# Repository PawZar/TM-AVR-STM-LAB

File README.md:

# Projekt centrali alarmowej
## TM-AVR-STM-LAB

Centrala alarmowa z hasłem , 6-wejść typu NC oraz wyjściem przekaźnika naruszenia typu NO.

## Cechy projektu:
* MCU: AtMega32A w obudowie TQFP44
* Wyświetlacz 2x16 ze sterownikiem HD44780
* Zasilanie 12V DC-IN Max:1,2A
* Zasilacznie czujek 12V DC ~1A obc.
* Wyjście naruszenia typu NO ~1A obciążenie styków
* Wejścia czujek NC wyzwalane stanem niskim
* Pamięć naruszeń
* Kontrola kontrastu wyświetlacza
* Diody LED statusu centrali (alarm,uzbrojenie,stan spoczynku,odliczanie)
* 6 przycisków w roli klawiatury (ESC,1-4,ENTER)
* Dioda LED zasilania

## Działanie centrali:

Centrala posiada 2 tryby, uzbrojony oraz nieuzbrojony. Po wciśnięciu przycisku ENTER następuje przejście do funkcji wpisywania hasła.
Do wpisywania hasła dostępne mamy przyciski 1-4, ENTER oraz ESC który kasuje błędnie wpisaną liczbę .
Po poprawnym wpisaniu hasła następuje odliczanie 20sekund symulujące czas na wyjście z mieszkania. Po upływie czasu uzbrajania centrali,
wejścia czujek aktywują się. Wejścia ustawione są w tryb NC ze zwarciem do GND, kiedy jedna z czujek przez minimum 1,6sek 
zostanie aktywowana zaczyna się przejście do funkcji wpisywania hasła na które ma się ponowne 20sekund. Po upływie tego czasu,
bądź 3-krotnym złym wpisaniu hasła następuje wyzwolenie alarmu i załączenie wyjścia. Podczas trwanai alarmu można przejść do funkcji 
wpisywania hasła przyciskiem ENTER. Po rozbrojeniu centrali po alarmie zapamiętane zostaje zdarzenie naruszenia systemu, po następnym uzbrojeniu
centrali błąd się kasuje.

## Mikrokontroler Atmega32A:

 * Taktowanie w projekcie: 16MHz zewnętrzne
 * Zasilanie układu: 5V DC
 * Programowanie : złącze ISP
 * 1kB EEPROM
 * 2kB SRAM
 * 32kB flash

## Zdjęcia schematu oraz płytki z programu EAGLE:

## Zdjęcia wykonanego układu:

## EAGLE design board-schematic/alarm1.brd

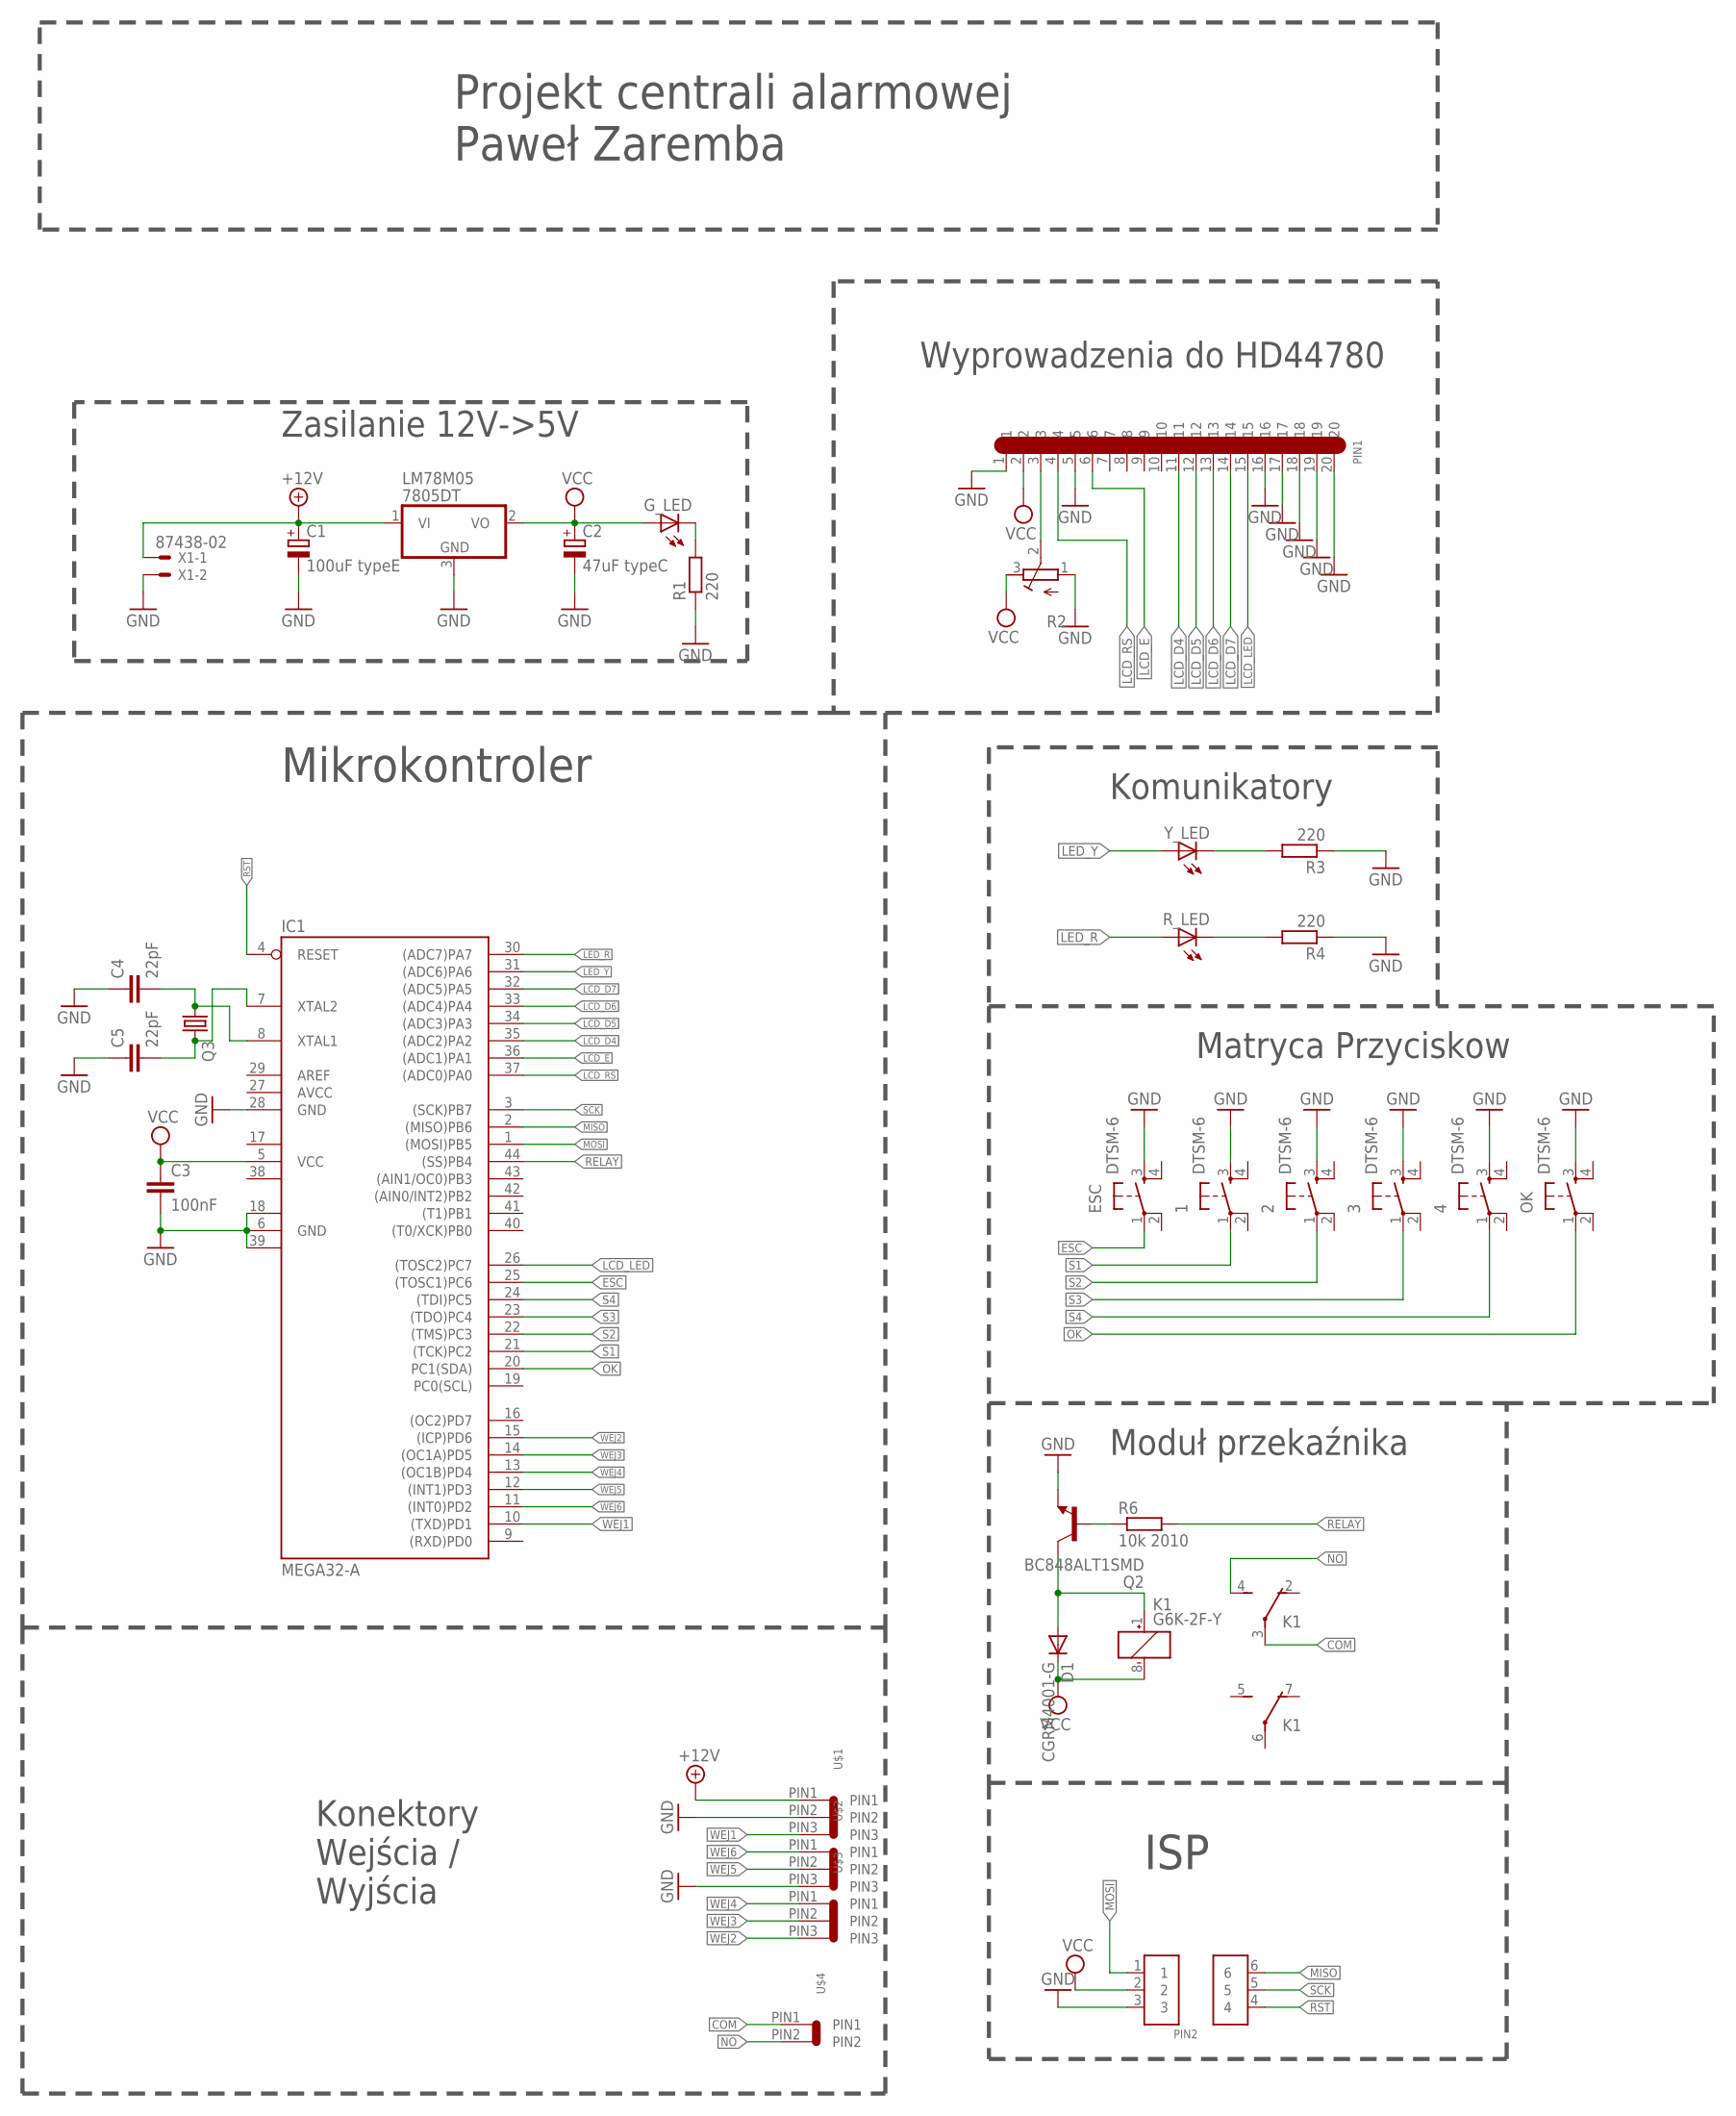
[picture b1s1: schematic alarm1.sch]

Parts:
1, 2, 3, 4: DTSM-6
C1: 100uF typeE; PANASONIC_E
C2: 47uF typeC; PANASONIC_C
C3: 100nF; C1206
C4, C5: 22pF; C1206
D1: CGRM4001-G; SOD-123_MINI-SMA
ESC: DTSM-6
G_LED: LEDCHIPLED_1206; CHIPLED_1206
IC1: MEGA32-A; TQFP44
K1: G6K-2F-Y
LM78M05: 7805DT; TO252
OK: DTSM-6
PIN1: SINGLE1X20
PIN2: 2X3_GOLDPIN; GOLD2X3
Q2: BC848ALT1SMD; SOT23
Q3: CRYSTALHC49UP; HC49UP
R1, R3, R4: 220; R1206
R2: R-TRIMM3314J; RTRIM3314J
R6: 10k 2010; R2010
R_LED: LEDCHIPLED_1206; CHIPLED_1206
U$1, U$2, U$3: GOLDPIN_SMD_1X3; GOLDPINSMD1X3
U$4: GOLDPIN_SMD_1X2; GOLDPINSMD1X2
X1: 87438-02
Y_LED: LEDCHIPLED_1206; CHIPLED_1206

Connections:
+12V: C1.+, LM78M05.1 (VI), U$1.PIN1, X1.1
AVCC: IC1.27 (AVCC)
COM: K1.3, U$4.PIN1
CRYSTAL_L: C5.2, IC1.7 (XTAL2), Q3.2
CRYSTAL_R: C4.2, IC1.8 (XTAL1), Q3.1
ESC: ESC.1, IC1.25 ((TOSC1)PC6)
GND: 1.3, 2.3, 3.3, 4.3, C1.-, C2.-, C3.2, C4.1, C5.1, ESC.3, IC1.6 (GND), IC1.18 (GND1), IC1.28 (GND), IC1.39 (GND2), LM78M05.3 (GND), OK.3, PIN1.1, PIN1.5, PIN1.16, PIN1.17, PIN1.18, PIN1.19, PIN1.20, PIN2.3, Q2.2 (E), R1.1, R2.1 (E), R3.1, R4.1, U$1.PIN2, U$2.PIN3, X1.2
LCD_D4: IC1.35 ((ADC2)PA2), PIN1.11
LCD_D5: IC1.34 ((ADC3)PA3), PIN1.12
LCD_D6: IC1.33 ((ADC4)PA4), PIN1.13
LCD_D7: IC1.32 ((ADC5)PA5), PIN1.14
LCD_E: IC1.36 ((ADC1)PA1), PIN1.6
LCD_LED: IC1.26 ((TOSC2)PC7), PIN1.15
LCD_RS: IC1.37 ((ADC0)PA0), PIN1.4
LED_R: IC1.30 ((ADC7)PA7), R_LED.A
LED_Y: IC1.31 ((ADC6)PA6), Y_LED.A
MISO: IC1.2 ((MISO)PB6), PIN2.6
MOSI: IC1.1 ((MOSI)PB5), PIN2.1
unnamed: D1.A, K1.1 (+), Q2.3 (C)
unnamed: G_LED.C, R1.2
unnamed: PIN1.3, R2.2 (S)
unnamed: R3.2, Y_LED.C
unnamed: R4.2, R_LED.C
unnamed: Q2.1 (B), R6.1
NO: K1.4 (S), U$4.PIN2
OK: IC1.20 (PC1(SDA)), OK.1
RELAY: IC1.44 ((SS)PB4), R6.2
RST: IC1.4 (RESET), PIN2.4
S1: 1.1, IC1.21 ((TCK)PC2)
S2: 2.1, IC1.22 ((TMS)PC3)
S3: 3.1, IC1.23 ((TDO)PC4)
S4: 4.1, IC1.24 ((TDI)PC5)
SCK: IC1.3 ((SCK)PB7), PIN2.5
VCC: C2.+, C3.1, D1.C, G_LED.A, IC1.5 (VCC), K1.8 (-), LM78M05.2 (VO), PIN1.2, PIN2.2, R2.3 (A)
VCC1: IC1.17 (VCC1)
VCC2: IC1.38 (VCC2)
WEJ1: IC1.10 ((TXD)PD1), U$1.PIN3
WEJ2: IC1.15 ((ICP)PD6), U$3.PIN3
WEJ3: IC1.14 ((OC1A)PD5), U$3.PIN2
WEJ4: IC1.13 ((OC1B)PD4), U$3.PIN1
WEJ5: IC1.12 ((INT1)PD3), U$2.PIN2
WEJ6: IC1.11 ((INT0)PD2), U$2.PIN1

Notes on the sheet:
Zasilanie 12V->5V
Wyprowadzenia do HD44780
Komunikatory
Matryca Przyciskow
ISP
Moduł przekaźnika
Konektory Wejścia / Wyjścia
Mikrokontroler
Projekt centrali alarmowej Paweł Zaremba

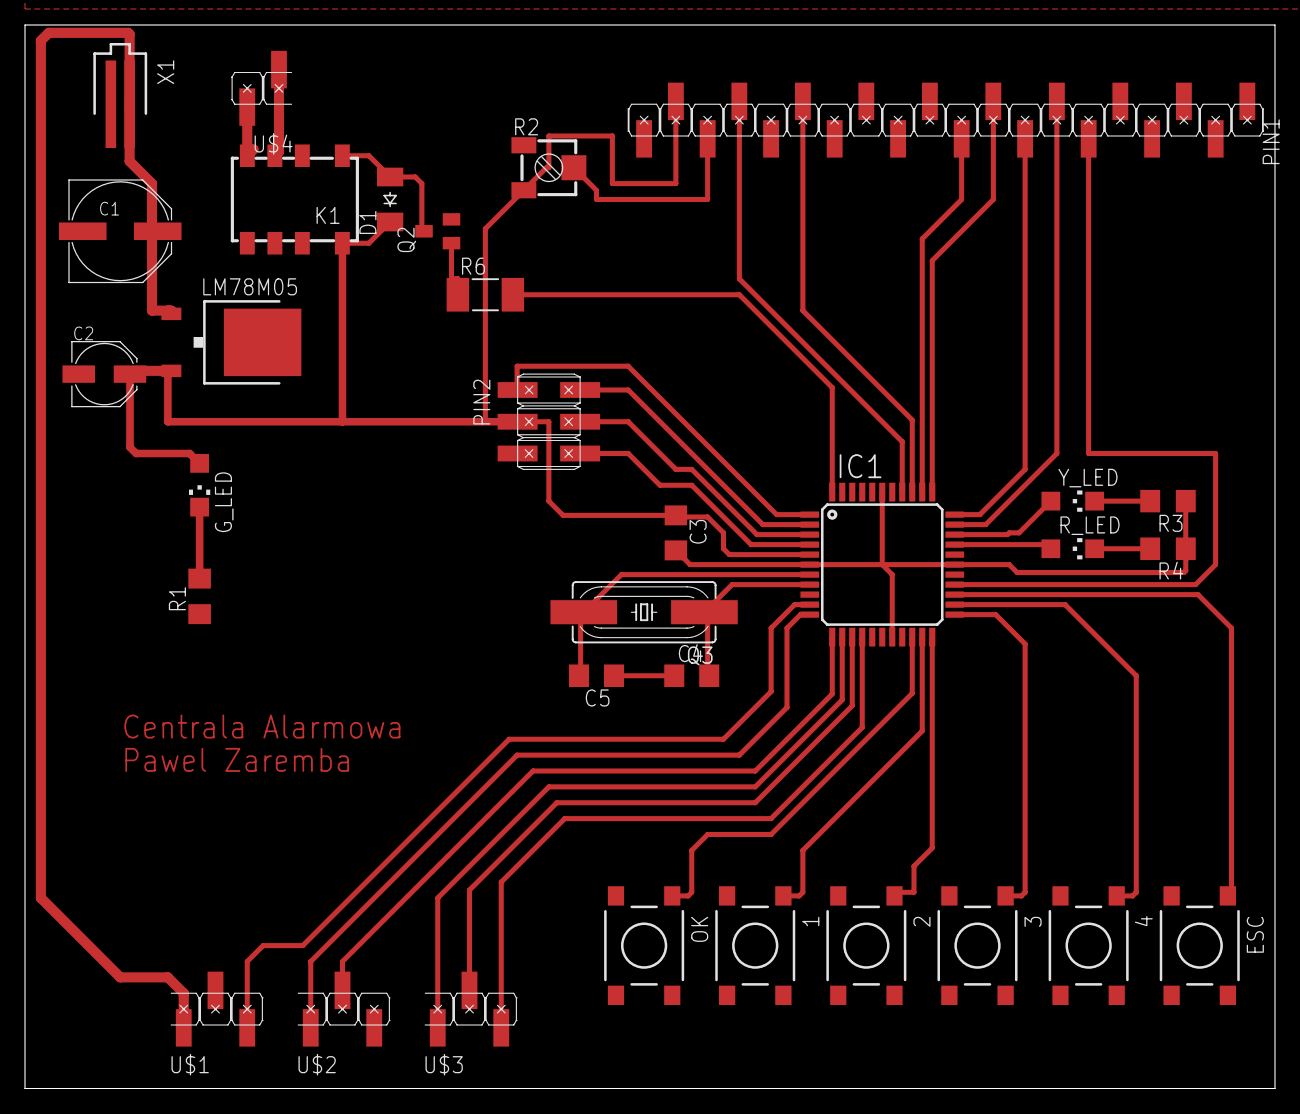
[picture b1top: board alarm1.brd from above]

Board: 2 copper layers, 100.0 x 85.1 mm, 32 parts (0 on the bottom side), 39 nets.

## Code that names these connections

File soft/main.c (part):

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#include <avr/alarm/HD44780.h>
#include "avr/alarm/HD44780.c"

#define LEDy (1<<PA6) //zolta dioda statusu
#define LEDr (1<<PA7) //czerwona dioda uzbrojenia

#define esc (1<<PC2) // esc
#define jeden (1<<PC3) // 1
#define dwa (1<<PC4) // 2
#define trzy (1<<PC5) // 3
#define cztery (1<<PC6) // 4
#define ok (1<<PC7) //  ok / uzbrajanie

#define relay (1<<PD0) // przekaznik

#define wej1 (1<<PD2) // wejscie Z1
#define wej2 (1<<PD3) // wejscie Z2
#define wej3 (1<<PD4) // wejscie Z3
#define wej4 (1<<PD5) // wejscie Z4
#define wej5 (1<<PD6) // wejscie Z5
#define wej6 (1<<PD7) // wejscie Z6


int main(void)
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		}

		else if(uzbrojenie==1){
		if(PIND & relay){
			PORTD ^= relay;
		}
		uzbrojenie=0;
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	{
		stanUzbrojony();

	if(PIND & wej1)
	{
	naruszenie1++;
		if(naruszenie1>=15){
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			naruszenie1=16;
		}
	}
	else if(!(PIND & wej1)){
		if(naruszenie1>=1){
		naruszenie1--;
		}
	}


	if(PIND & wej2)
	{
	naruszenie2++;
		if(naruszenie2>=15){
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			naruszenie2=16;
		}
	}
	else if(!(PIND & wej2)){
		if(naruszenie2>=1){
		naruszenie2--;
		}
	}


	if(PIND & wej3)
	{
	naruszenie3++;
		if(naruszenie3>=15){
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			naruszenie3=16;
		}
	}
	else if(!(PIND & wej3)){
		if(naruszenie3>=1){
		naruszenie3--;
		}
	}


	if(PIND & wej4)
	{
	naruszenie4++;
		if(naruszenie4>=15){
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			naruszenie4=16;
		}
	}
	else if(!(PIND & wej4)){
		if(naruszenie4>=1){
		naruszenie4--;
		}
	}


	if(PIND & wej5)
	{
	naruszenie5++;
		if(naruszenie5>=15){
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			naruszenie5=16;
		}
	}
	else if(!(PIND & wej5)){
		if(naruszenie5>=1){
		naruszenie5--;
		}
	}

	if(PIND & wej6)
	{
	naruszenie6++;
		if(naruszenie6>=15){
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			naruszenie6=16;
		}
	}
	else if(!(PIND & wej6)){
		if(naruszenie6>=1){
		naruszenie6--;
		}
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
	if(alarm==1)
	{
		if(!(PIND & relay)){
			PORTD ^= relay;
		}
		if(!(PINA & LEDr)){
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	if(PINA & LEDy){
		PORTA^= LEDy;
	}
	if(PINA & relay){
		PORTA^= relay;
	}
	t=time%20;
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			LCD_GoTo(0,1);
			LCD_WriteText("*****");
		}
		if(!(PINC & esc))
		{

			wyjsciowa=3;
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
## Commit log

2021-10-26 Projektv0.1
    Opis
2022-02-02 Add soft
    Dodanie kodu, bibliotek oraz wsadów .o .hex .d
2022-02-02 Sch/Board/Foto
2022-02-02 Update README.md
    opis
